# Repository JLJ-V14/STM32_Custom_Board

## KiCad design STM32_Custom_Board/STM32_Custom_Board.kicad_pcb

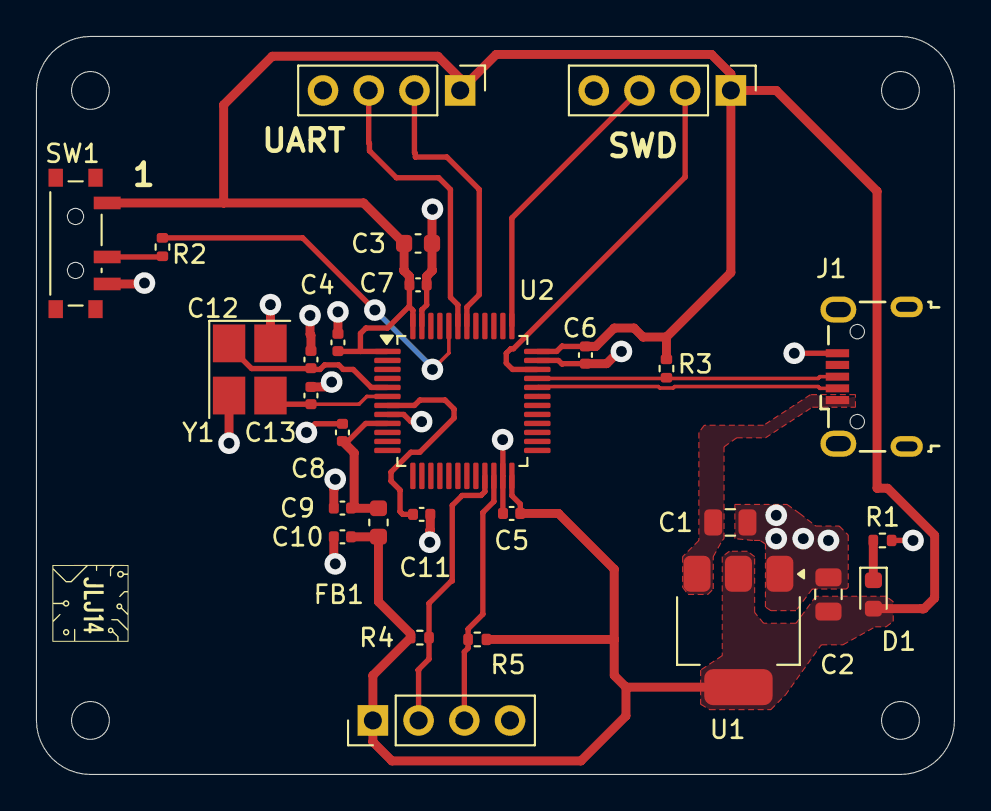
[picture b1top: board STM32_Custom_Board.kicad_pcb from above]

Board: 2 copper layers, 51.0 x 41.0 mm, 32 parts (0 on the bottom side), 18 nets.

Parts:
C1, C2: 22u; C_0805_2012Metric
C3: 10u; C_0603_1608Metric
C4, C5, C6, C7, C11: 100n; C_0402_1005Metric
C8: 10n; C_0402_1005Metric
C9, C10: 1u; C_0402_1005Metric
C12, C13: 10p; C_0402_1005Metric
D1: RED; LED_0603_1608Metric
FB1: 120R; L_0603_1608Metric
H1, H2, H3, H4: MountingHole; MountingHole_2.1mm
J1: USB_B_Micro; USB_Micro-B_Wuerth_629105150521
J2, J3, J4: Conn_01x04_Male; PinHeader_1x04_P2.54mm_Vertical
R1, R3, R4, R5: 1k5; R_0402_1005Metric
R2: 10k; R_0402_1005Metric
SW1: SW_SPDT; SW_SPDT_PCM12
U1: AMS1117-3.3; SOT-223-3_TabPin2
U2: STM32F103C8T6; LQFP-48_7x7mm_P0.5mm
Y1: 16MHz; Crystal_SMD_3225-4Pin_3.2x2.5mm_HandSoldering

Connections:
+3.3V: C2.1, C3.1, C4.1, C5.1, C6.1, C7.1, C10.1, D1.2 (A), FB1.2, J2.1, J3.1, J4.1, R3.1, R4.1, R5.1, SW1.1 (A), U1.2 (VO), U2.1 (VBAT), U2.24 (VDD), U2.36 (VDD), U2.48 (VDD)
+3.3VA: C8.1, C9.1, FB1.1, U2.9 (VDDA)
/BOOT0: R2.2, U2.44 (BOOT0)
/HSE_IN: C12.1, U2.5 (PD0), Y1.1
/HSE_OUT: C13.1, U2.6 (PD1), Y1.3
/I2CS_SCL: J4.2, R4.2, U2.21 (PB10)
/I2CS_SDA: J4.3, R5.2, U2.22 (PB11)
/NRST: C11.1, U2.7 (NRST)
/PWR_LED_K: D1.1 (K), R1.1
/SWCLK: J2.3, U2.37 (PA14)
/SWDIO: J2.2, U2.34 (PA13)
/SW_BOOT0: R2.1, SW1.2 (B)
/USART1_TX: J3.2, U2.42 (PB6)
/USART_RX: J3.3, U2.43 (PB7)
/USB_D+: J1.3 (D+), R3.2, U2.33 (PA12)
/USB_D-: J1.2 (D-), U2.32 (PA11)
GND: C1.2, C2.2, C3.2, C4.2, C5.2, C6.2, C7.2, C8.2, C9.2, C10.2, C11.2, C12.2, C13.2, J1.5 (GND), J2.4, J3.4, J4.4, R1.2, SW1.3 (C), U1.1 (GND), U2.8 (VSSA), U2.23 (VSS), U2.35 (VSS), U2.47 (VSS), Y1.2, Y1.4
VBUS: C1.1, J1.1 (VBUS), U1.3 (VI)

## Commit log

2025-05-11 Initial import of existing contents
2025-05-22 Decoupling capacitors for NRST and VDA added
2025-05-24 Switch in boot pin added
    Quartz Crystal added
2025-05-25 micro USB B added
    Serial debugging connections added
    UART connections added
    I2C connections added
    Power supply LDO added
2025-05-25 Schematic polished and finished
2025-05-29 Footprints assigned
2025-05-29 PCB constraints added
2025-05-29 Decoupling capacitors positioned in PCB
2025-05-31 Component placement finished
2025-05-31 Board outline finished and connectors put in place
2025-06-07 Routing of signals finished
2025-06-08 Routing process finished
2025-06-08 PCB board finished
2025-06-08 Image added to the PCB
2025-06-08 Bill of materials generated
2025-06-08 All fabrication files generateed
